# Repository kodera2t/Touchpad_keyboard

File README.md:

Ultra thin and tiny keyboard for tiny computers is finished! I made a small interface board which transferring from touching position information to ASCII code, which is sending out 4800bps (as same as PS/2 and chatpad of Xbox360) to computer.
# Touchpad_keyboard
initial submission

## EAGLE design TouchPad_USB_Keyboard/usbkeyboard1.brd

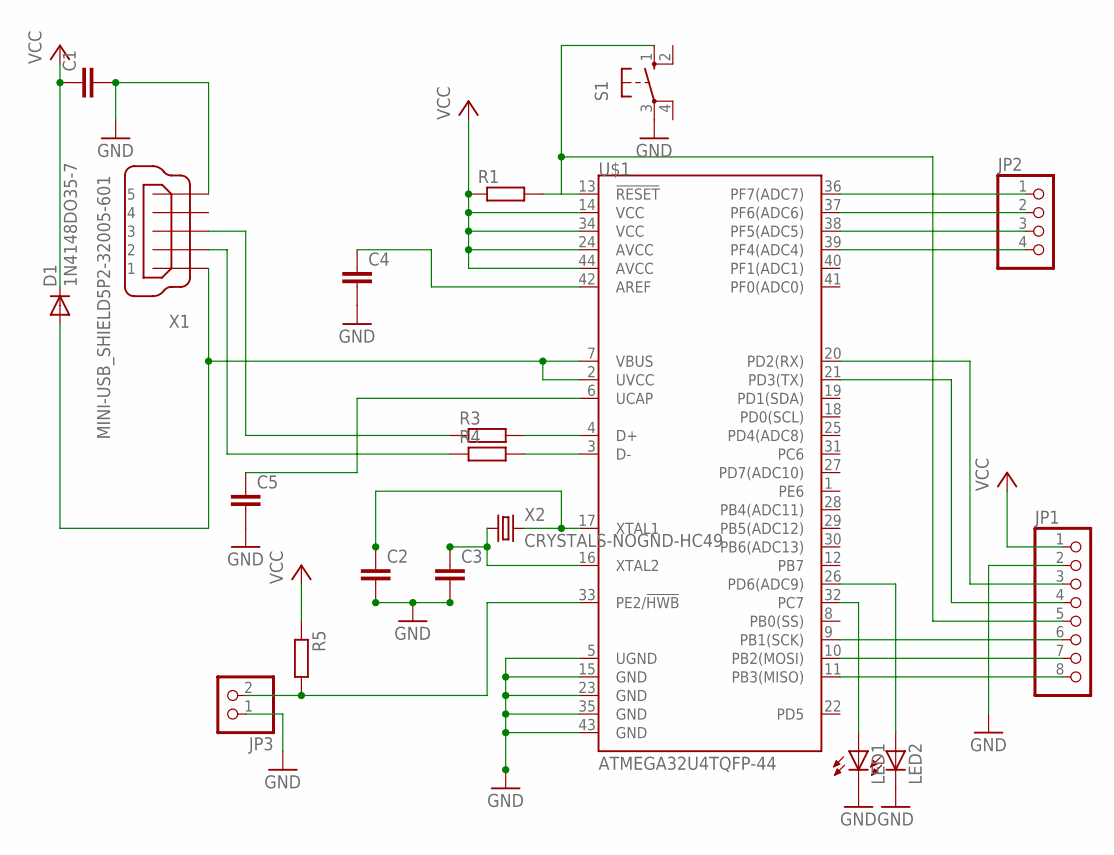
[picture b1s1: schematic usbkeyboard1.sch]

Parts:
C1, C2, C3, C4, C5: CC0603; C0603
D1: 1N4148DO35-7; DO35-7
JP1: PINHD-1X8; 1X08
JP2: PINHD-1X4; 1X04
JP3: PINHD-1X2; 1X02
LED1, LED2: LED_ELD260; LED_LD260
R1, R3, R4, R5: RR0603; R0603
S1: 10-XX; B3F-10XX
U$1: ATMEGA32U4TQFP-44; TQFP44
X1: MINI-USB_SHIELD5P2-32005-601; 32005-601
X2: CRYSTALS-NOGND-HC49; HC49

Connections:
GND: C1.2, C2.2, C3.2, C4.2, C5.2, JP1.2, JP3.1, LED1.K (C), LED2.K (C), S1.3, U$1.5 (UGND), U$1.15 (GND), U$1.23 (GND), U$1.35 (GND), U$1.43 (GND), X1.5
unnamed: JP1.8, U$1.11 (PB3(MISO))
unnamed: JP1.5, R1.2, S1.1 (S), U$1.13 (!RESET)
unnamed: D1.A, U$1.2 (UVCC), U$1.7 (VBUS), X1.1
unnamed: R3.2, U$1.4 (D+)
unnamed: R4.2, U$1.3 (D-)
unnamed: R4.1, X1.2
unnamed: R3.1, X1.3
unnamed: C2.1, U$1.17 (XTAL1), X2.2
unnamed: C3.1, U$1.16 (XTAL2), X2.1
unnamed: JP1.7, U$1.10 (PB2(MOSI))
unnamed: JP1.6, U$1.9 (PB1(SCK))
unnamed: JP1.4, U$1.21 (PD3(TX))
unnamed: JP1.3, U$1.20 (PD2(RX))
unnamed: JP2.1, U$1.36 (PF7(ADC7))
unnamed: JP2.2, U$1.37 (PF6(ADC6))
unnamed: JP2.3, U$1.38 (PF5(ADC5))
unnamed: JP2.4, U$1.39 (PF4(ADC4))
unnamed: LED2.A, U$1.26 (PD6(ADC9))
unnamed: LED1.A, U$1.32 (PC7)
unnamed: JP3.2, R5.2, U$1.33 (PE2/!HWB)
unnamed: C4.1, U$1.42 (AREF)
unnamed: C5.1, U$1.6 (UCAP)
VCC: C1.1, D1.C, JP1.1, R1.1, R5.1, U$1.14 (VCC), U$1.24 (AVCC), U$1.34 (VCC), U$1.44 (AVCC)

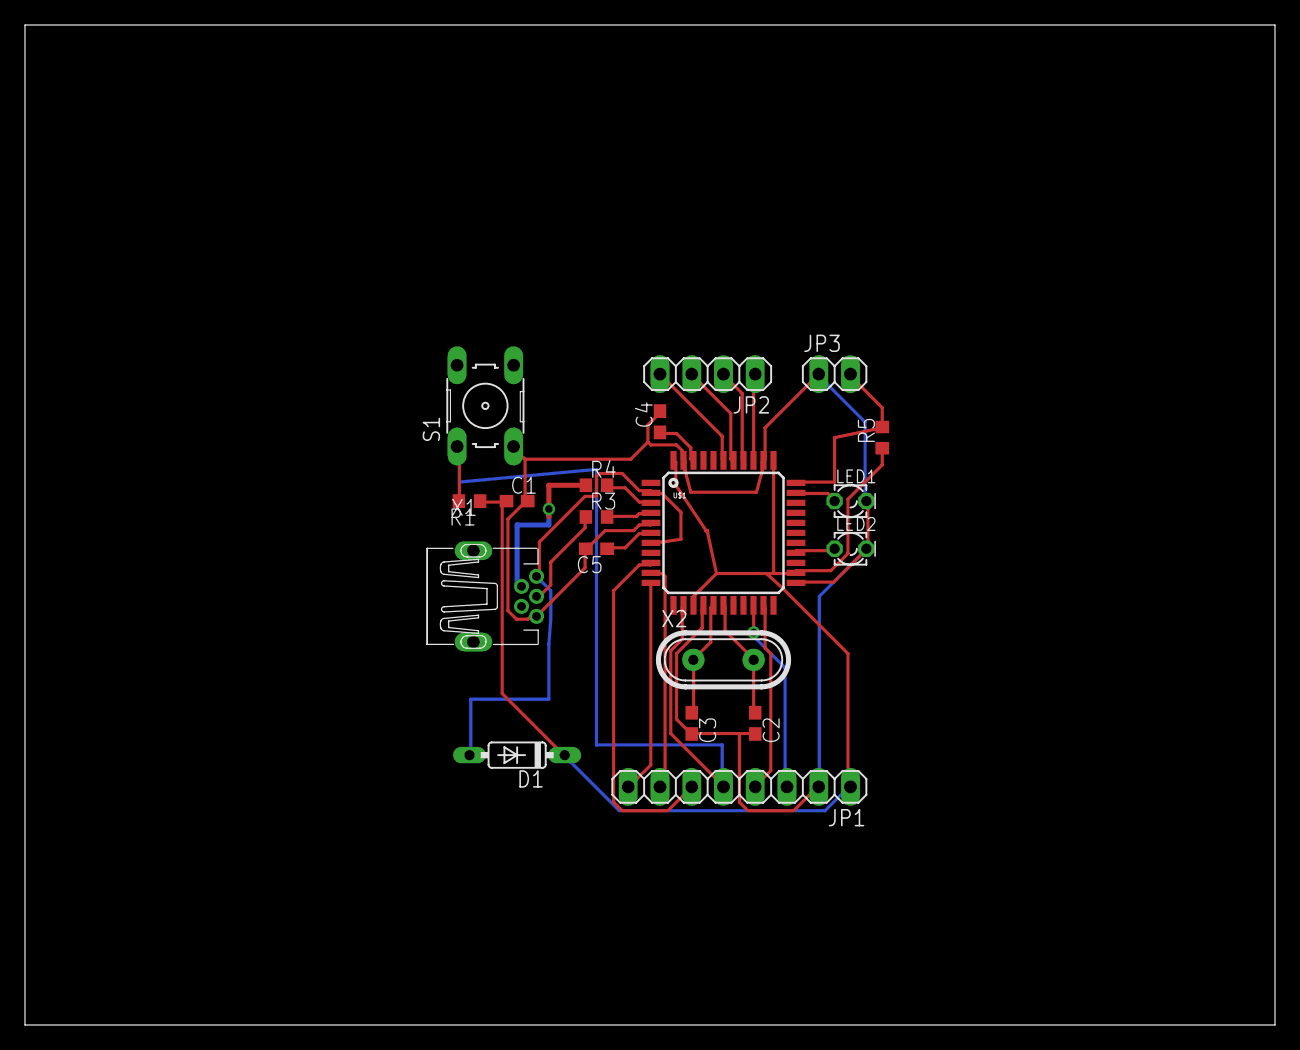
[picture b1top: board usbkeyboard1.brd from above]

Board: 2 copper layers, 100.0 x 80.0 mm, 19 parts (0 on the bottom side), 24 nets.

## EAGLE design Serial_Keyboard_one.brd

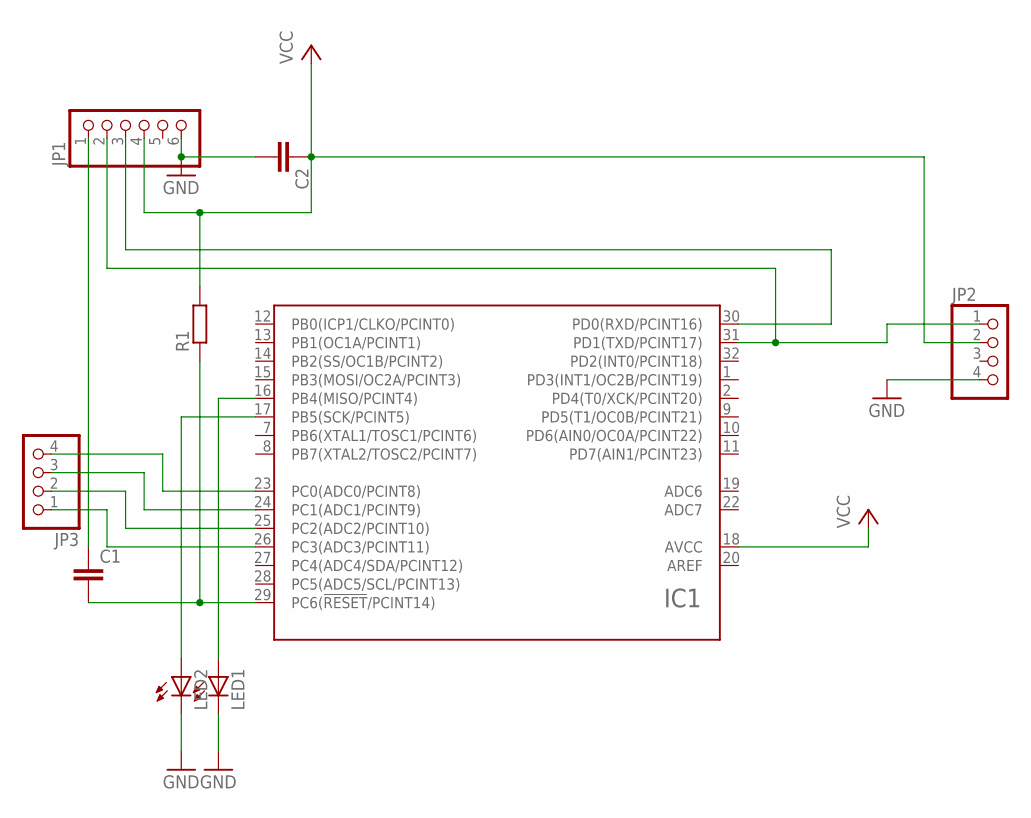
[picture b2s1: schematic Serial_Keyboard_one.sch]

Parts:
C1, C2: CC0603; C0603
IC1: ATMEGA48/88/168/328-AU; TQFP32-08
JP1: PINHD-1X6; 1X06
JP2, JP3: PINHD-1X4; 1X04
LED1, LED2: LED_ELD260; LED_LD260
R1: RR0603; R0603

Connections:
GND: C2.2, IC1.3 (GND), IC1.5 (GND), IC1.21 (GND), JP1.6, JP2.4, LED1.K (C), LED2.K (C)
unnamed: C1.1, JP1.1
unnamed: C1.2, IC1.29 (PC6(!RESET!/PCINT14)), R1.1
unnamed: IC1.31 (PD1(TXD/PCINT17)), JP1.2, JP2.1
unnamed: IC1.30 (PD0(RXD/PCINT16)), JP1.3
unnamed: IC1.23 (PC0(ADC0/PCINT8)), JP3.4
unnamed: IC1.24 (PC1(ADC1/PCINT9)), JP3.3
unnamed: IC1.25 (PC2(ADC2/PCINT10)), JP3.2
unnamed: IC1.26 (PC3(ADC3/PCINT11)), JP3.1
unnamed: IC1.17 (PB5(SCK/PCINT5)), LED2.A
unnamed: IC1.16 (PB4(MISO/PCINT4)), LED1.A
UCC: IC1.4 (UCC), IC1.6 (UCC)
VCC: C2.1, IC1.18 (AVCC), JP1.4, JP2.2, R1.2

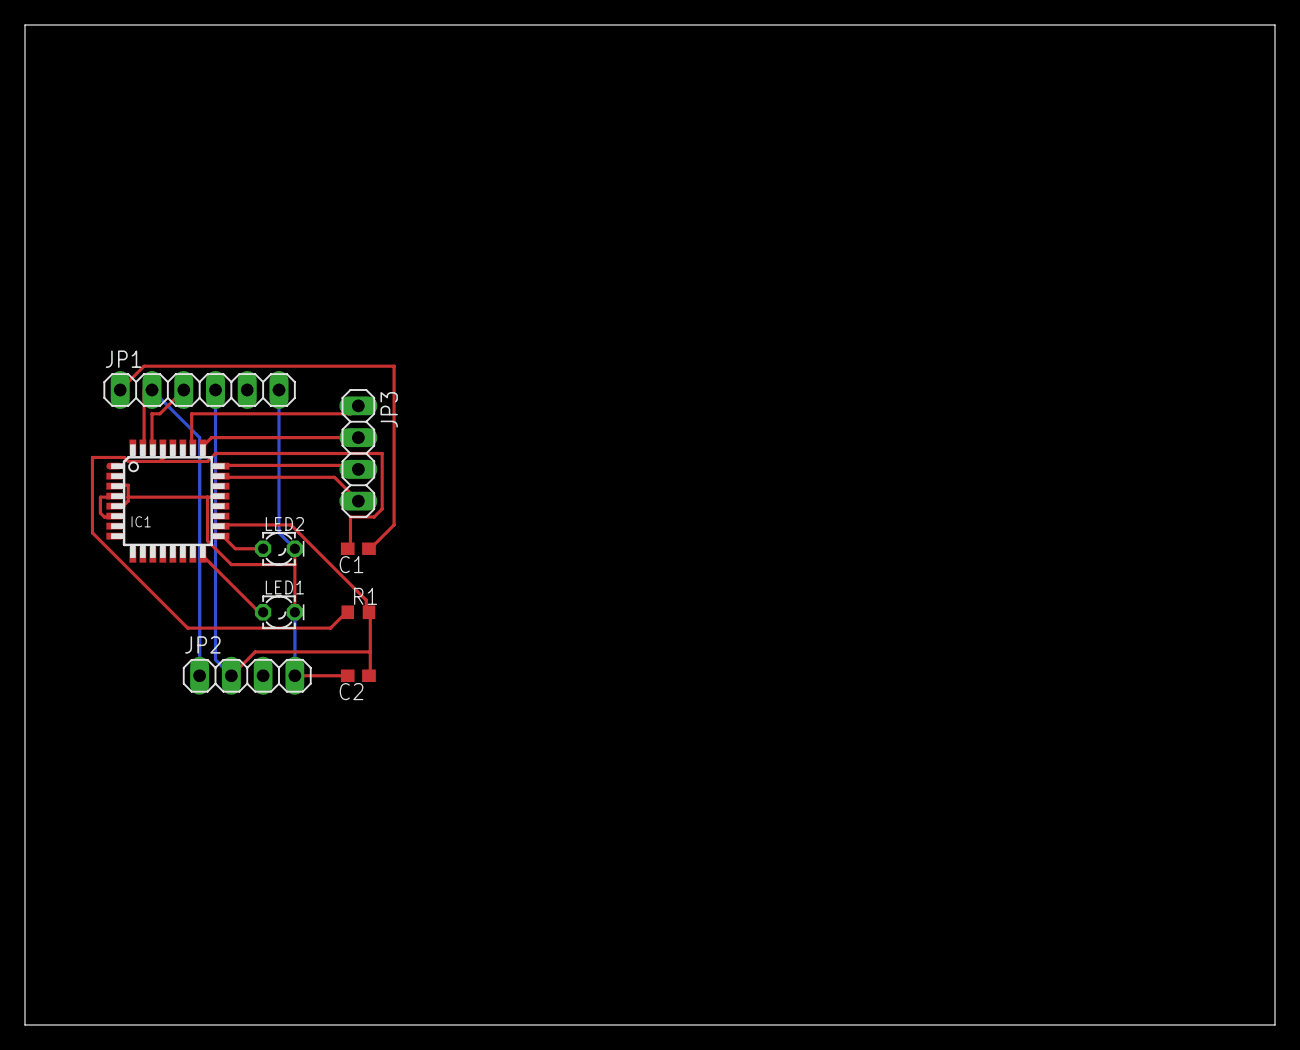
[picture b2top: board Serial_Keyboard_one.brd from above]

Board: 2 copper layers, 100.0 x 80.0 mm, 9 parts (0 on the bottom side), 13 nets.

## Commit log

2015-02-27 initial submission
2015-03-20 USB version are here

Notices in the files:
parts and their libraries:
SparkFun-DigitalIC: Licensing: Creative Commons ShareAlike 4.0 International - https://creativecommons.org/licenses/by-sa/4.0
